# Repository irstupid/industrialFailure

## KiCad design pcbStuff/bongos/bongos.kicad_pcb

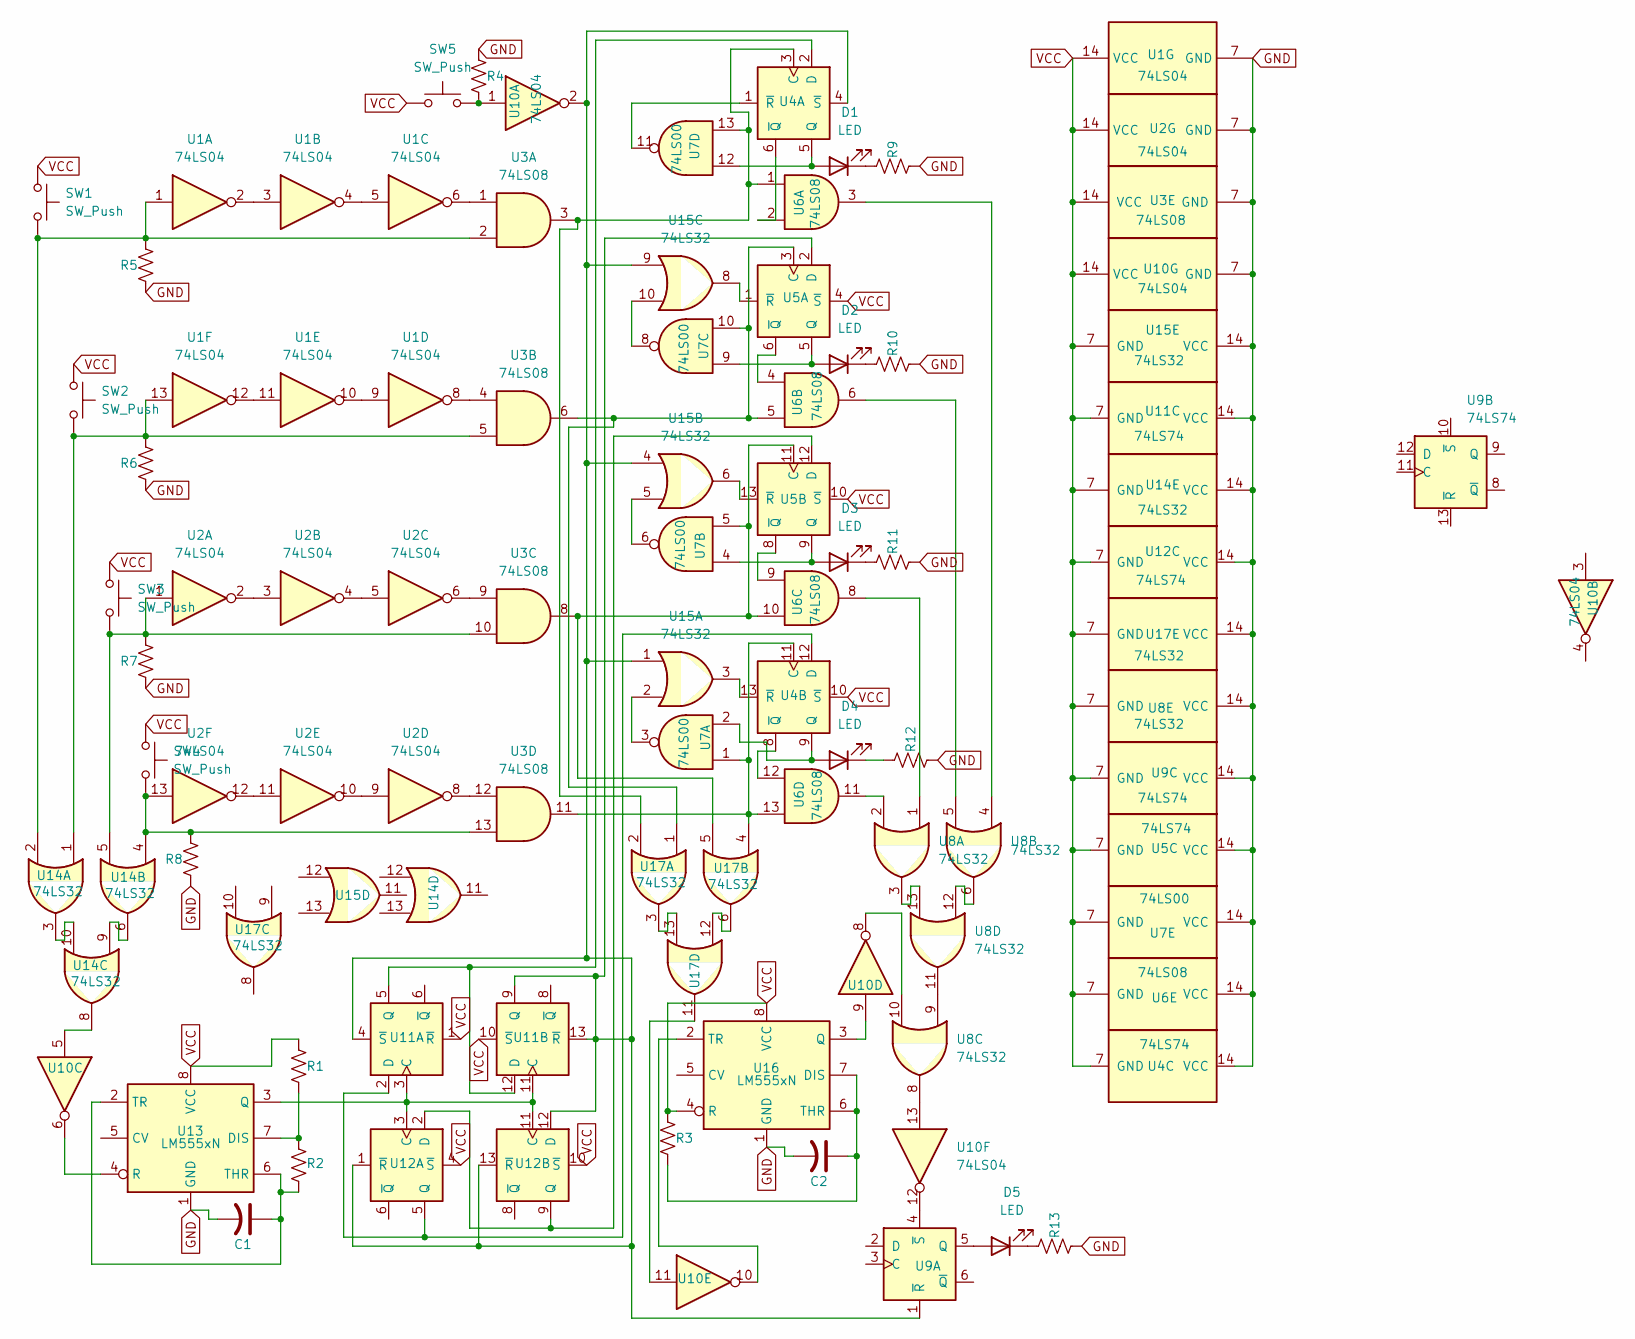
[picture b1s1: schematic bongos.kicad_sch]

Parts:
C1, C2: C_US; CP_Radial_D5.0mm_P2.50mm
D1, D2, D3, D4, D5: LED; LED_D5.0mm
R1, R2, R3, R4, R5, R6, R7, R8, R9, R10, R11, R12, R13: R_US; R_Axial_DIN0207_L6.3mm_D2.5mm_P7.62mm_Horizontal
SW1, SW2, SW3, SW4: SW_Push; SW_PUSH-12mm
SW5: SW_Push; SW_PUSH_6mm
U1, U2, U10: 74LS04; DIP-14_W7.62mm
U3, U6: 74LS08; DIP-14_W7.62mm
U4, U5, U9, U11, U12: 74LS74; DIP-14_W7.62mm
U7: 74LS00; DIP-14_W7.62mm
U8, U14, U15, U17: 74LS32; DIP-14_W7.62mm
U13, U16: LM555xN; DIP-8_W7.62mm

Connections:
GND: C1.2, C2.2, R4.1, R5.1, R6.1, R7.1, R8.1, R9.2, R10.2, R11.2, R12.2, R13.2, U1.7 (GND), U2.7 (GND), U3.7 (GND), U4.14 (VCC), U5.14 (VCC), U6.14 (VCC), U7.14 (VCC), U8.14 (VCC), U9.14 (VCC), U10.7 (GND), U11.14 (VCC), U12.14 (VCC), U13.1 (GND), U14.14 (VCC), U15.14 (VCC), U16.1 (GND), U17.14 (VCC)
unnamed: D1.2 (A), U4.5 (Q), U7.12
unnamed: D1.1 (K), R9.1
unnamed: D2.2 (A), U5.5 (Q), U7.9
unnamed: D2.1 (K), R10.1
unnamed: D3.2 (A), U5.9 (Q), U7.4
unnamed: D3.1 (K), R11.1
unnamed: D4.2 (A), U4.9 (Q), U7.2
unnamed: D4.1 (K), R12.1
unnamed: D5.2 (A), U9.5 (Q)
unnamed: D5.1 (K), R13.1
unnamed: R4.2, SW5.2, U10.1
unnamed: R5.2, SW1.2, U1.1, U3.2, U14.2
unnamed: R6.2, SW2.2, U1.13, U3.5, U14.1
unnamed: R7.2, SW3.2, U2.1, U3.10, U14.5
unnamed: R8.2, SW4.2, U2.13, U3.13, U14.4
unnamed: U1.2, U1.3
unnamed: U1.4, U1.5
unnamed: U1.6, U3.1
unnamed: U1.8, U3.4
unnamed: U1.9, U1.10
unnamed: U1.11, U1.12
unnamed: U2.2, U2.3
unnamed: U2.4, U2.5
unnamed: U2.6, U3.9
unnamed: U2.8, U3.12
unnamed: U2.9, U2.10
unnamed: U2.11, U2.12
unnamed: U3.3, U4.3 (C), U6.1, U7.13, U17.2
unnamed: U4.6 (~Q), U6.2
unnamed: U4.1 (~R), U7.11
unnamed: U3.11, U4.11 (C), U6.13, U7.1, U17.4
unnamed: U4.8 (~Q), U6.12
unnamed: U4.13 (~R), U15.3
unnamed: U3.6, U5.3 (C), U6.5, U7.10, U17.1
unnamed: U5.6 (~Q), U6.4
unnamed: U5.1 (~R), U15.8
unnamed: U3.8, U5.11 (C), U6.10, U7.5, U17.5
unnamed: U5.8 (~Q), U6.9
unnamed: U5.13 (~R), U15.6
unnamed: U6.3, U8.4
unnamed: U6.6, U8.5
unnamed: U6.8, U8.1
unnamed: U6.11, U8.2
unnamed: U8.9, U8.11
unnamed: U8.6, U8.12
unnamed: U8.3, U8.13
unnamed: U9.4 (~S), U10.12
unnamed: U10.5, U14.8
unnamed: U8.10, U10.8
unnamed: U10.11, U17.11
unnamed: U8.8, U10.13
unnamed: U11.3 (C), U11.11 (C), U12.3 (C), U12.11 (C), U13.3 (Q)
unnamed: U4.12 (D), U11.2 (D), U12.5 (Q)
unnamed: U4.2 (D), U11.5 (Q), U11.12 (D)
unnamed: U4.4 (~S), U5.2 (D), U9.1 (~R), U10.2, U11.4 (~S), U11.9 (Q), U11.13 (~R), U12.1 (~R), U12.12 (D), U12.13 (~R), U15.1, U15.4, U15.9
unnamed: U5.12 (D), U12.2 (D), U12.9 (Q)
unnamed: R1.2, R2.1, U13.7 (DIS)
unnamed: U10.6, U13.4 (R)
unnamed: C1.1, R2.2, U13.2 (TR), U13.6 (THR)
unnamed: U14.6, U14.9
unnamed: U14.3, U14.10
unnamed: U7.3, U15.2
unnamed: U7.6, U15.5
unnamed: U7.8, U15.10
unnamed: C2.1, R3.2, U16.6 (THR), U16.7 (DIS)
unnamed: U10.9, U16.3 (Q)
unnamed: U10.10, U16.2 (TR)
unnamed: U17.6, U17.12
unnamed: U17.3, U17.13
VCC: R1.1, R3.1, SW1.1, SW2.1, SW3.1, SW4.1, SW5.1, U1.14 (VCC), U2.14 (VCC), U3.14 (VCC), U4.7 (GND), U4.10 (~S), U5.4 (~S), U5.7 (GND), U5.10 (~S), U6.7 (GND), U7.7 (GND), U8.7 (GND), U9.7 (GND), U10.14 (VCC), U11.1 (~R), U11.7 (GND), U11.10 (~S), U12.4 (~S), U12.7 (GND), U12.10 (~S), U13.8 (VCC), U14.7 (GND), U15.7 (GND), U16.4 (R), U16.8 (VCC), U17.7 (GND)

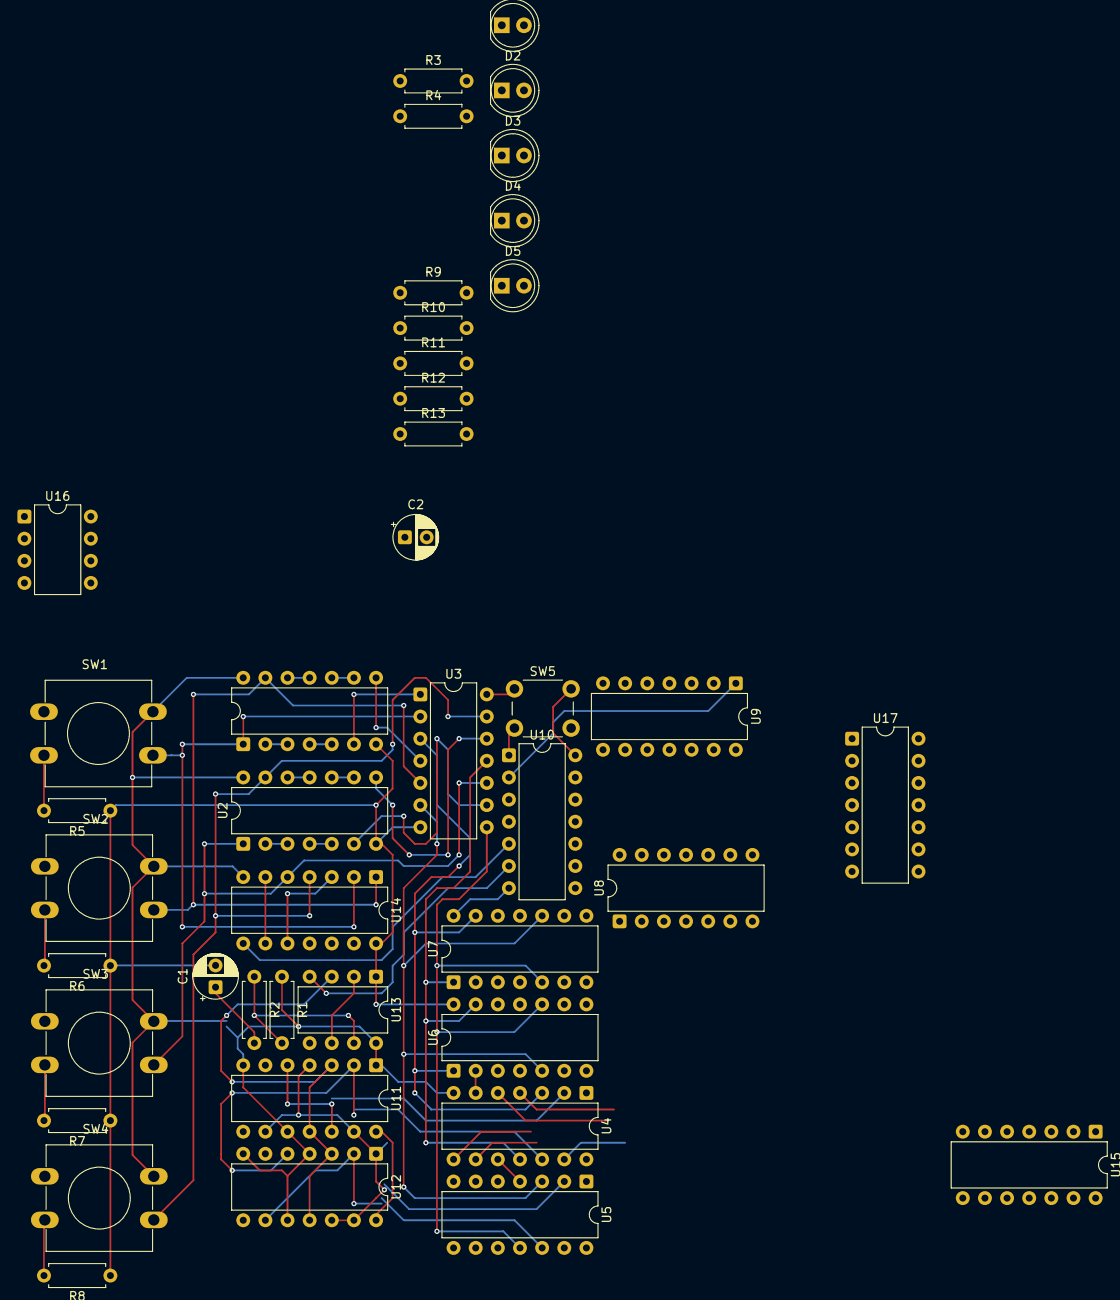
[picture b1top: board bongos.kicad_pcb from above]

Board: 2 copper layers, 42 parts (0 on the bottom side), 71 nets.

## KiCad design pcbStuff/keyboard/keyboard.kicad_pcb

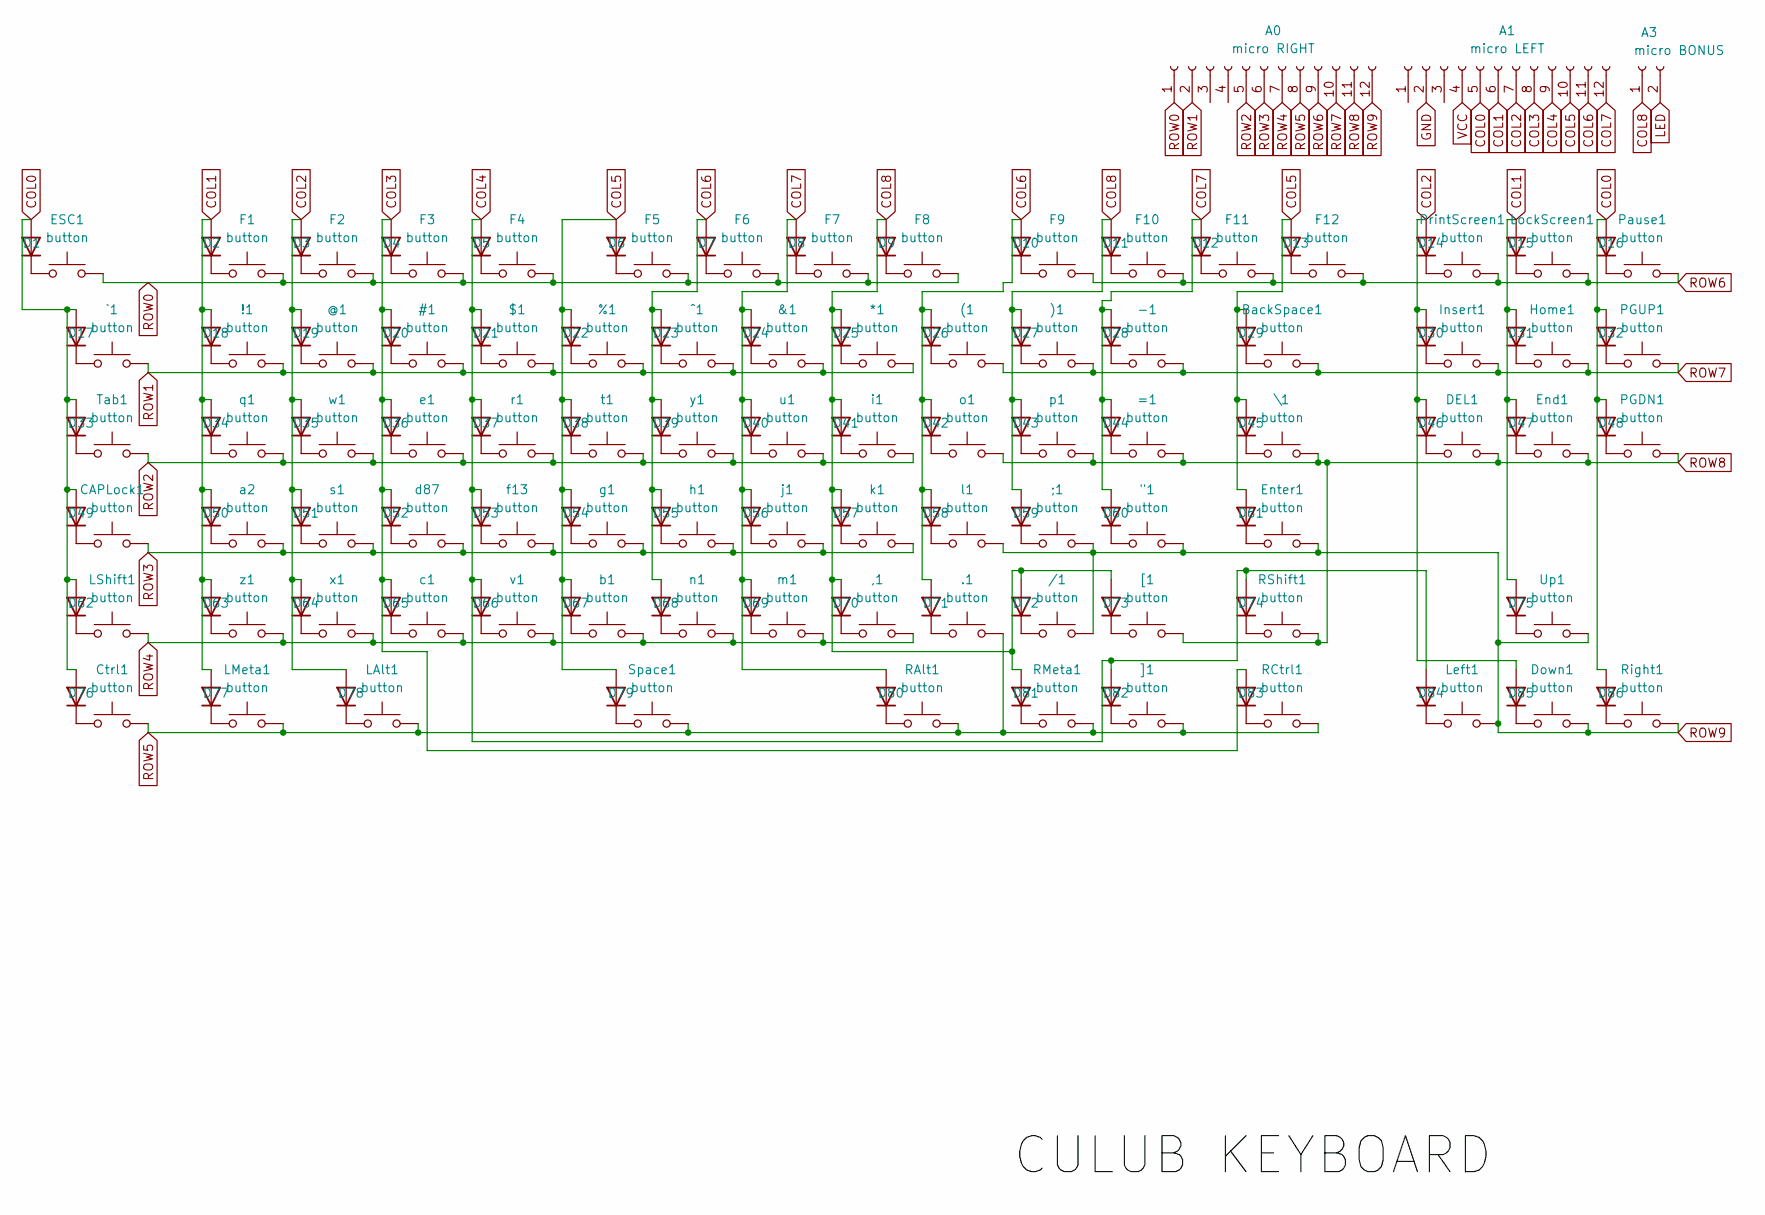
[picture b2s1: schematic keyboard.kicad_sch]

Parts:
!1: button; SW_Cherry_MX_1.00u_PCB
"1: button; SW_Cherry_MX_1.00u_PCB
$1: button; SW_Cherry_MX_1.00u_PCB
%1: button; SW_Cherry_MX_1.00u_PCB
&1: button; SW_Cherry_MX_1.00u_PCB
(1: button; SW_Cherry_MX_1.00u_PCB
)1: button; SW_Cherry_MX_1.00u_PCB
*1: button; SW_Cherry_MX_1.00u_PCB
,1: button; SW_Cherry_MX_1.00u_PCB
-1: button; SW_Cherry_MX_1.00u_PCB
.1: button; SW_Cherry_MX_1.00u_PCB
/1: button; SW_Cherry_MX_1.00u_PCB
;1: button; SW_Cherry_MX_1.00u_PCB
=1: button; SW_Cherry_MX_1.00u_PCB
@1: button; SW_Cherry_MX_1.00u_PCB
A0: micro RIGHT; PinHeader_1x12_P2.54mm_Vertical
A1: micro LEFT; PinHeader_1x12_P2.54mm_Vertical
A3: micro BONUS; PinHeader_1x02_P2.54mm_Vertical
BackSpace1: button; SW_Cherry_MX_1.00u_PCB
CAPLock1: button; SW_Cherry_MX_1.00u_PCB
Ctrl1: button; SW_Cherry_MX_1.00u_PCB
D1, D2, D3, D4, D5, D6, D7, D8, D9, D10, D11, D12, D13, D14, D15, D16, D17, D18, D19, D20, D21, D22, D23, D24, D25, D26, D27, D28, D29, D30, D31, D32, D33, D34, D35, D36, D37, D38, D39, D40, D41, D42, D43, D44, D45, D46, D47, D48, D49, D50, D51, D52, D53, D54, D55, D56, D57, D58, D59, D60, D61, D62, D63, D64, D65, D66, D67, D68, D69, D70, D71, D72, D73, D74, D75, D76, D77, D78, D79, D80, D81, D82, D83, D84, D85, D86: 1N4148WT; D_SOD-523
DEL1: button; SW_Cherry_MX_1.00u_PCB
Down1: button; SW_Cherry_MX_1.00u_PCB
ESC1: button; SW_Cherry_MX_1.00u_PCB
End1: button; SW_Cherry_MX_1.00u_PCB
Enter1: button; SW_Cherry_MX_1.00u_PCB
F1, F2, F3, F4, F5, F6, F7, F8, F9, F10, F11, F12: button; SW_Cherry_MX_1.00u_PCB
Home1: button; SW_Cherry_MX_1.00u_PCB
Insert1: button; SW_Cherry_MX_1.00u_PCB
LAlt1: button; SW_Cherry_MX_1.00u_PCB
LMeta1: button; SW_Cherry_MX_1.00u_PCB
LShift1: button; SW_Cherry_MX_1.00u_PCB
Left1: button; SW_Cherry_MX_1.00u_PCB
LockScreen1: button; SW_Cherry_MX_1.00u_PCB
PGDN1: button; SW_Cherry_MX_1.00u_PCB
PGUP1: button; SW_Cherry_MX_1.00u_PCB
Pause1: button; SW_Cherry_MX_1.00u_PCB
PrintScreen1: button; SW_Cherry_MX_1.00u_PCB
RAlt1: button; SW_Cherry_MX_1.00u_PCB
RCtrl1: button; SW_Cherry_MX_1.00u_PCB
RMeta1: button; SW_Cherry_MX_1.00u_PCB
RShift1: button; SW_Cherry_MX_1.00u_PCB
Right1: button; SW_Cherry_MX_1.00u_PCB
Space1: button; SW_Cherry_MX_1.00u_PCB
Tab1: button; SW_Cherry_MX_1.00u_PCB
Up1: button; SW_Cherry_MX_1.00u_PCB
[1: button; SW_Cherry_MX_1.00u_PCB
\1: button; SW_Cherry_MX_1.00u_PCB
]1: button; SW_Cherry_MX_1.00u_PCB
^1: button; SW_Cherry_MX_1.00u_PCB
`1: button; SW_Cherry_MX_1.00u_PCB
a2: button; SW_Cherry_MX_1.00u_PCB
b1: button; SW_Cherry_MX_1.00u_PCB
c1: button; SW_Cherry_MX_1.00u_PCB
d87: button; SW_Cherry_MX_1.00u_PCB
e1: button; SW_Cherry_MX_1.00u_PCB
f13: button; SW_Cherry_MX_1.00u_PCB
g1: button; SW_Cherry_MX_1.00u_PCB
h1: button; SW_Cherry_MX_1.00u_PCB
i1: button; SW_Cherry_MX_1.00u_PCB
j1: button; SW_Cherry_MX_1.00u_PCB
k1: button; SW_Cherry_MX_1.00u_PCB
l1: button; SW_Cherry_MX_1.00u_PCB
m1: button; SW_Cherry_MX_1.00u_PCB
n1: button; SW_Cherry_MX_1.00u_PCB
o1: button; SW_Cherry_MX_1.00u_PCB
p1: button; SW_Cherry_MX_1.00u_PCB
q1: button; SW_Cherry_MX_1.00u_PCB
r1: button; SW_Cherry_MX_1.00u_PCB
s1: button; SW_Cherry_MX_1.00u_PCB
t1: button; SW_Cherry_MX_1.00u_PCB
u1: button; SW_Cherry_MX_1.00u_PCB
v1: button; SW_Cherry_MX_1.00u_PCB
w1: button; SW_Cherry_MX_1.00u_PCB
x1: button; SW_Cherry_MX_1.00u_PCB
y1: button; SW_Cherry_MX_1.00u_PCB
z1: button; SW_Cherry_MX_1.00u_PCB

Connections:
COL0: A1.5, D1.2 (A), D16.2 (A), D17.2 (A), D32.2 (A), D33.2 (A), D48.2 (A), D49.2 (A), D62.2 (A), D76.2 (A), D86.2 (A)
COL1: A1.6, D2.2 (A), D15.2 (A), D18.2 (A), D31.2 (A), D34.2 (A), D47.2 (A), D50.2 (A), D63.2 (A), D75.2 (A), D77.2 (A)
COL2: A1.7, D3.2 (A), D14.2 (A), D19.2 (A), D30.2 (A), D35.2 (A), D46.2 (A), D51.2 (A), D64.2 (A), D78.2 (A), D85.2 (A)
COL3: A1.8, D4.2 (A), D20.2 (A), D36.2 (A), D52.2 (A), D65.2 (A), D83.2 (A)
COL4: A1.9, D5.2 (A), D21.2 (A), D37.2 (A), D53.2 (A), D66.2 (A), D74.2 (A), D82.2 (A), D84.2 (A)
COL5: A1.10, D6.2 (A), D13.2 (A), D22.2 (A), D29.2 (A), D38.2 (A), D45.2 (A), D54.2 (A), D61.2 (A), D67.2 (A), D79.2 (A)
COL6: A1.11, D7.2 (A), D10.2 (A), D23.2 (A), D26.2 (A), D39.2 (A), D42.2 (A), D55.2 (A), D58.2 (A), D68.2 (A), D71.2 (A)
COL7: A1.12, D8.2 (A), D12.2 (A), D24.2 (A), D28.2 (A), D40.2 (A), D44.2 (A), D56.2 (A), D60.2 (A), D69.2 (A), D80.2 (A)
COL8: A3.1, D9.2 (A), D11.2 (A), D25.2 (A), D27.2 (A), D41.2 (A), D43.2 (A), D57.2 (A), D59.2 (A), D70.2 (A), D72.2 (A), D73.2 (A), D81.2 (A)
GND: A1.2
LED: A3.2
unnamed: D1.1 (K), ESC1.1
unnamed: D2.1 (K), F1.1
unnamed: D3.1 (K), F2.1
unnamed: D4.1 (K), F3.1
unnamed: D5.1 (K), F4.1
unnamed: D6.1 (K), F5.1
unnamed: D7.1 (K), F6.1
unnamed: D8.1 (K), F7.1
unnamed: D9.1 (K), F8.1
unnamed: D10.1 (K), F9.1
unnamed: D11.1 (K), F10.1
unnamed: D12.1 (K), F11.1
unnamed: D13.1 (K), F12.1
unnamed: D14.1 (K), PrintScreen1.1
unnamed: D15.1 (K), LockScreen1.1
unnamed: D16.1 (K), Pause1.1
unnamed: D17.1 (K), `1.1
unnamed: !1.1, D18.1 (K)
unnamed: @1.1, D19.1 (K)
unnamed: $1.1, D21.1 (K)
unnamed: %1.1, D22.1 (K)
unnamed: D23.1 (K), ^1.1
unnamed: &1.1, D24.1 (K)
unnamed: *1.1, D25.1 (K)
unnamed: (1.1, D26.1 (K)
unnamed: )1.1, D27.1 (K)
unnamed: -1.1, D28.1 (K)
unnamed: BackSpace1.1, D29.1 (K)
unnamed: D30.1 (K), Insert1.1
unnamed: D31.1 (K), Home1.1
unnamed: D32.1 (K), PGUP1.1
unnamed: D33.1 (K), Tab1.1
unnamed: D34.1 (K), q1.1
unnamed: D35.1 (K), w1.1
unnamed: D36.1 (K), e1.1
unnamed: D37.1 (K), r1.1
unnamed: D38.1 (K), t1.1
unnamed: D39.1 (K), y1.1
unnamed: D40.1 (K), u1.1
unnamed: D41.1 (K), i1.1
unnamed: D42.1 (K), o1.1
unnamed: D43.1 (K), p1.1
unnamed: =1.1, D44.1 (K)
unnamed: D45.1 (K), \1.1
unnamed: D46.1 (K), DEL1.1
unnamed: D47.1 (K), End1.1
unnamed: D48.1 (K), PGDN1.1
unnamed: CAPLock1.1, D49.1 (K)
unnamed: D50.1 (K), a2.1
unnamed: D51.1 (K), s1.1
unnamed: D52.1 (K), d87.1
unnamed: D53.1 (K), f13.1
unnamed: D54.1 (K), g1.1
unnamed: D55.1 (K), h1.1
unnamed: D56.1 (K), j1.1
unnamed: D57.1 (K), k1.1
unnamed: D58.1 (K), l1.1
unnamed: ;1.1, D59.1 (K)
unnamed: "1.1, D60.1 (K)
unnamed: D61.1 (K), Enter1.1
unnamed: D62.1 (K), LShift1.1
unnamed: D63.1 (K), z1.1
unnamed: D64.1 (K), x1.1
unnamed: D65.1 (K), c1.1
unnamed: D66.1 (K), v1.1
unnamed: D67.1 (K), b1.1
unnamed: D68.1 (K), n1.1
unnamed: D69.1 (K), m1.1
unnamed: ,1.1, D70.1 (K)
unnamed: .1.1, D71.1 (K)
unnamed: /1.1, D72.1 (K)
unnamed: D73.1 (K), [1.1
unnamed: D74.1 (K), RShift1.1
unnamed: D75.1 (K), Up1.1
unnamed: Ctrl1.1, D76.1 (K)
unnamed: D77.1 (K), LMeta1.1
unnamed: D78.1 (K), LAlt1.1
unnamed: D79.1 (K), Space1.1
unnamed: D80.1 (K), RAlt1.1
unnamed: D81.1 (K), RMeta1.1
unnamed: D82.1 (K), ]1.1
unnamed: D83.1 (K), RCtrl1.1
unnamed: D84.1 (K), Left1.1
unnamed: D85.1 (K), Down1.1
unnamed: D86.1 (K), Right1.1
ROW0: A0.1, ESC1.2, F1.2, F2.2, F3.2, F4.2, F5.2, F6.2, F7.2, F8.2
ROW2: A0.5, Tab1.2, e1.2, i1.2, q1.2, r1.2, t1.2, u1.2, w1.2, y1.2
ROW3: A0.6, CAPLock1.2, a2.2, d87.2, f13.2, g1.2, h1.2, j1.2, k1.2, s1.2
ROW4: ,1.2, A0.7, LShift1.2, b1.2, c1.2, m1.2, n1.2, v1.2, x1.2, z1.2
ROW5: .1.2, A0.8, Ctrl1.2, LAlt1.2, LMeta1.2, RAlt1.2, RCtrl1.2, RMeta1.2, Space1.2, ]1.2
ROW6: A0.9, F9.2, F10.2, F11.2, F12.2, LockScreen1.2, Pause1.2, PrintScreen1.2
ROW7: (1.2, )1.2, -1.2, A0.10, BackSpace1.2, Home1.2, Insert1.2, PGUP1.2
ROW8: =1.2, A0.11, DEL1.2, End1.2, PGDN1.2, RShift1.2, [1.2, \1.2, o1.2, p1.2
ROW9: "1.2, /1.2, ;1.2, A0.12, Down1.2, Enter1.2, Left1.2, Right1.2, Up1.2, l1.2
VCC: A1.4

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
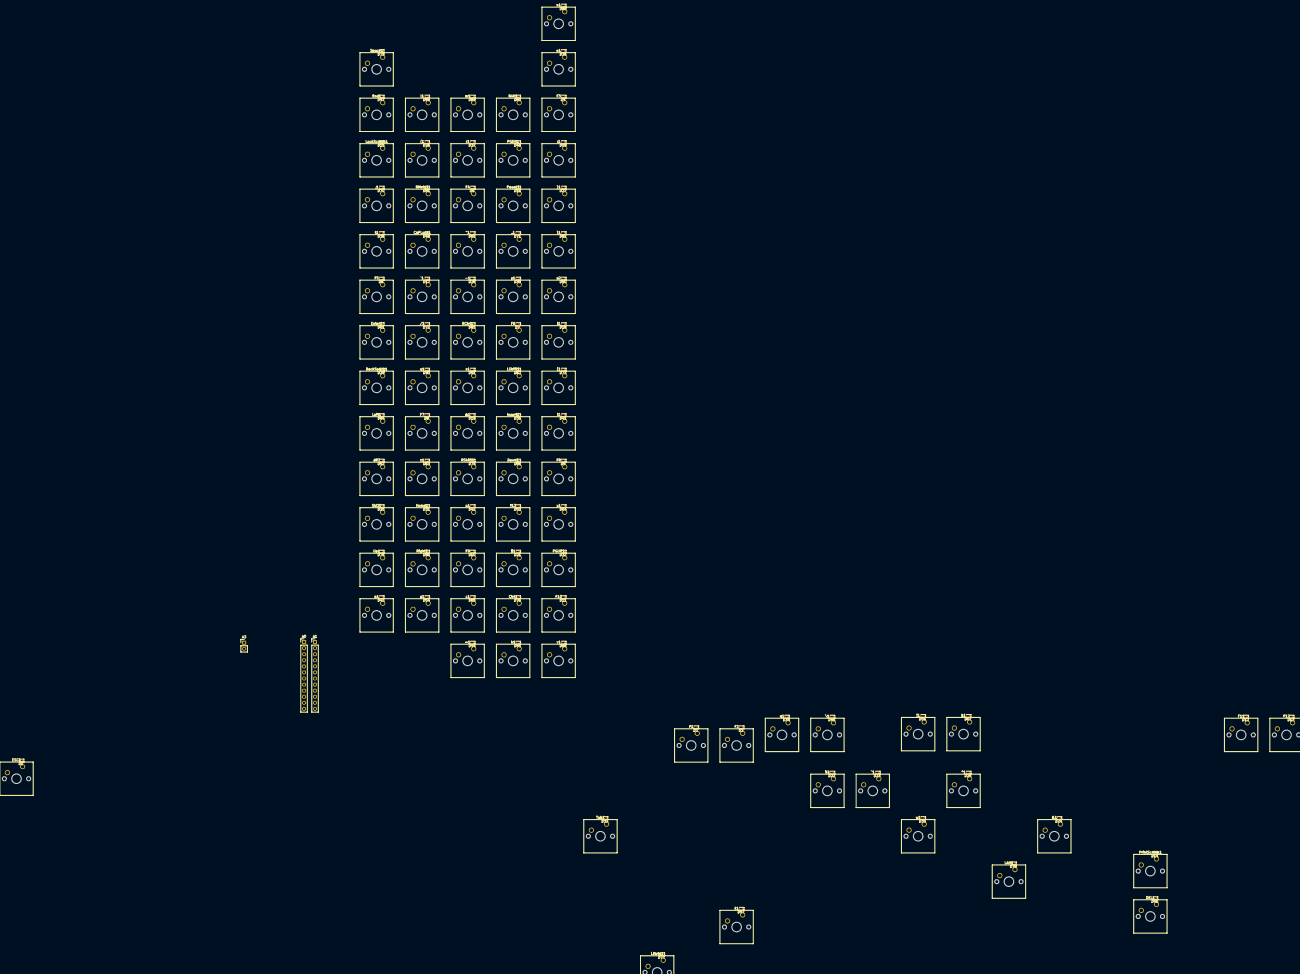
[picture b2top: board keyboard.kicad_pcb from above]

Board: 2 copper layers, 175 parts (0 on the bottom side), 105 nets.

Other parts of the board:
SW20: button; SW_Cherry_MX_1.00u_PCB

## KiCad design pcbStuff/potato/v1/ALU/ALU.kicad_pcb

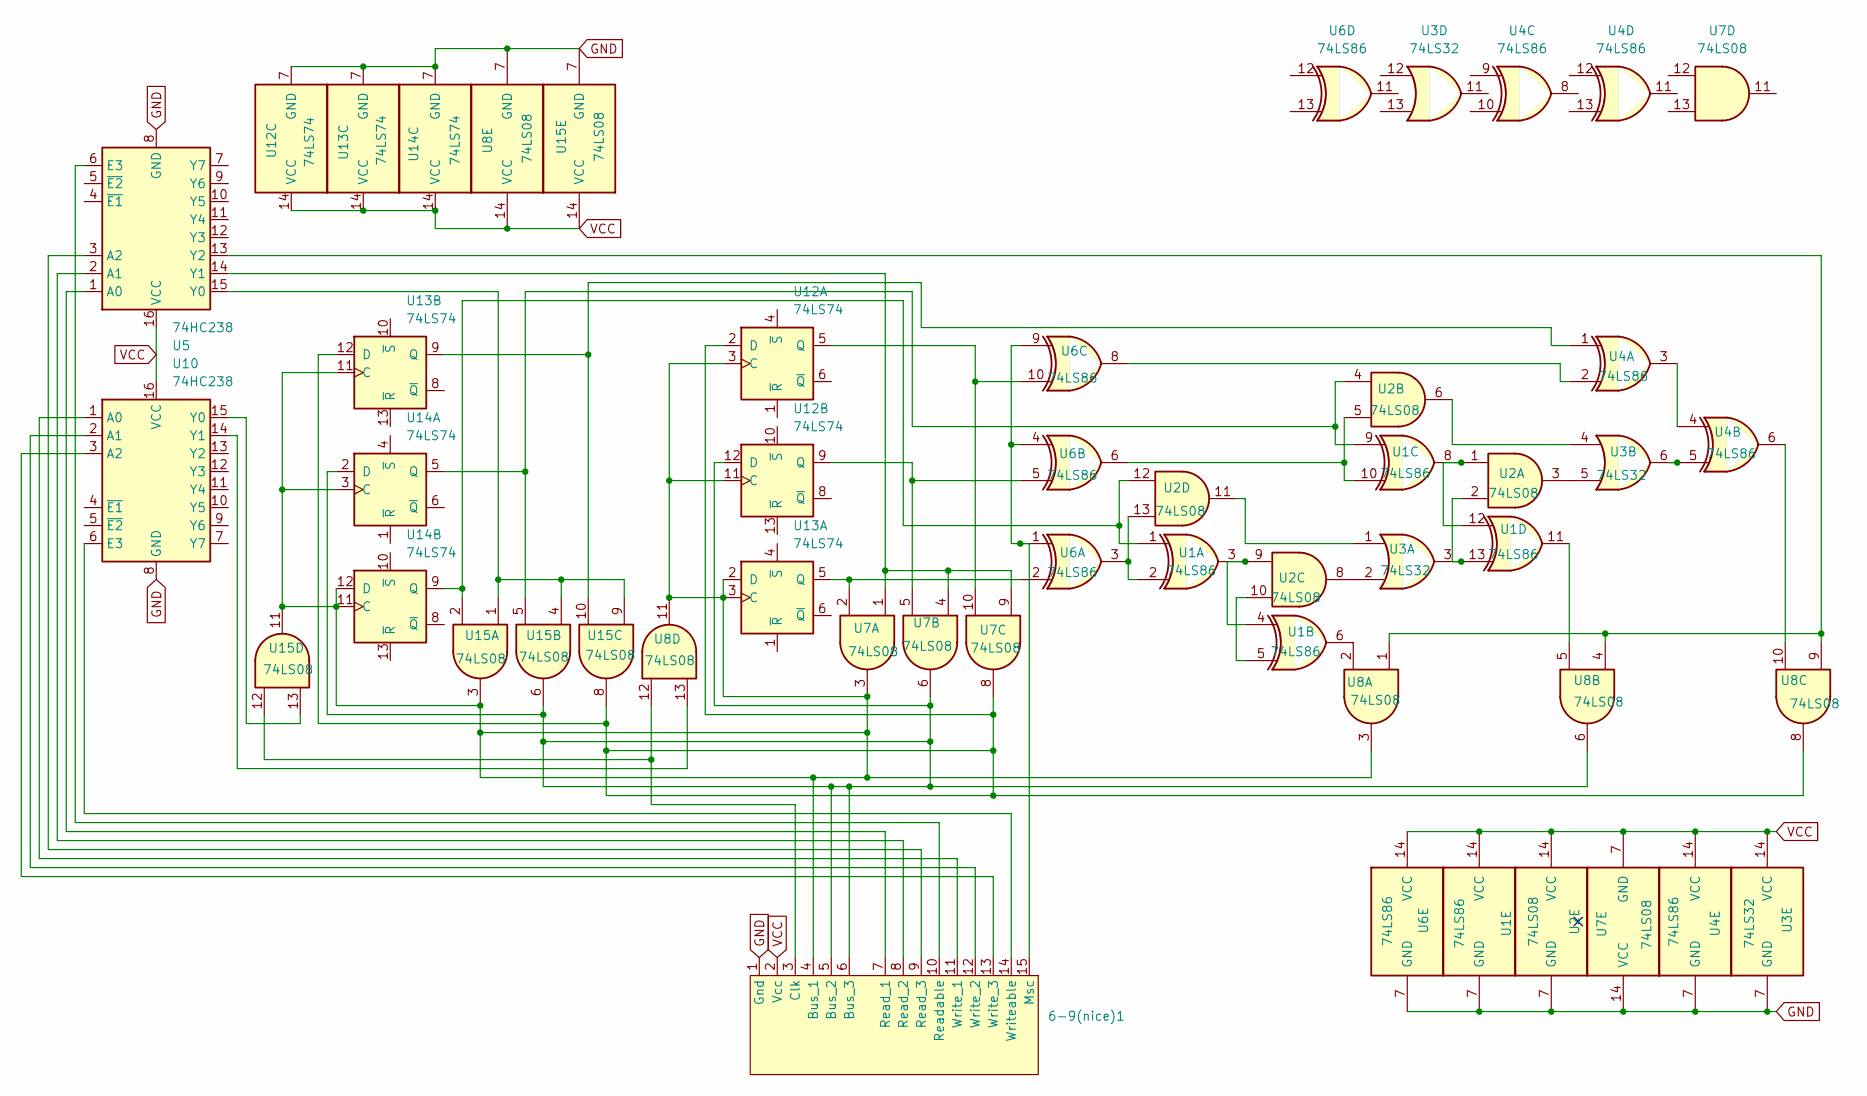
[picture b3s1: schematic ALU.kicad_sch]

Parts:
6-9(nice)1: PinHeader_1x15_P2.54mm_Vertical
U1, U4, U6: 74LS86; DIP-14_W7.62mm
U2, U7, U8, U15: 74LS08; DIP-14_W7.62mm
U3: 74LS32; DIP-14_W7.62mm
U5, U10: 74HC238; DIP-16_W7.62mm
U12, U13, U14: 74LS74; DIP-14_W7.62mm

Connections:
GND: 6-9(nice)1.1 (Gnd), U1.7 (GND), U2.7 (GND), U3.7 (GND), U4.7 (GND), U5.8 (GND), U6.7 (GND), U7.14 (VCC), U8.7 (GND), U10.8 (GND), U12.7 (GND), U13.7 (GND), U14.7 (GND), U15.7 (GND)
unnamed: 6-9(nice)1.4 (Bus_1), U7.3, U8.3, U8.11, U12.3 (C), U12.11 (C), U13.2 (D), U13.3 (C), U13.11 (C), U14.3 (C), U14.11 (C), U14.12 (D), U15.3, U15.11
unnamed: 6-9(nice)1.5 (Bus_2), 6-9(nice)1.6 (Bus_3), U7.6, U8.6, U12.12 (D), U14.2 (D), U15.6
unnamed: 6-9(nice)1.3 (Clk), U8.12, U15.12
unnamed: 6-9(nice)1.15 (Msc), U6.1, U6.4, U6.9
unnamed: 6-9(nice)1.7 (Read_1), U5.1 (A0)
unnamed: 6-9(nice)1.8 (Read_2), U5.2 (A1)
unnamed: 6-9(nice)1.9 (Read_3), U5.3 (A2)
unnamed: 6-9(nice)1.10 (Readable), U5.6 (E3)
unnamed: 6-9(nice)1.11 (Write_1), U10.1 (A0)
unnamed: 6-9(nice)1.12 (Write_2), U10.2 (A1)
unnamed: 6-9(nice)1.13 (Write_3), U10.3 (A2)
unnamed: 6-9(nice)1.14 (Writeable), U10.6 (E3)
unnamed: U1.2, U2.13, U6.3
unnamed: U1.3, U1.4, U2.9
unnamed: U1.5, U2.10
unnamed: U1.6, U8.2
unnamed: U1.10, U2.5, U6.6
unnamed: U1.11, U8.5
unnamed: U1.8, U1.12, U2.1
unnamed: U1.13, U2.2, U3.3
unnamed: U2.3, U3.5
unnamed: U2.6, U3.4
unnamed: U2.8, U3.2
unnamed: U2.11, U3.1
unnamed: U3.6, U4.5
unnamed: U4.2, U6.8
unnamed: U4.3, U4.4
unnamed: U4.6, U8.10
unnamed: U5.15 (Y0), U15.1, U15.4, U15.9
unnamed: U5.14 (Y1), U7.1, U7.4, U7.9
unnamed: U5.13 (Y2), U8.1, U8.4, U8.9
unnamed: U10.15 (Y0), U15.13
unnamed: U8.13, U10.14 (Y1)
unnamed: U7.8, U8.8, U12.2 (D), U13.12 (D), U15.8
unnamed: U6.10, U7.10, U12.5 (Q)
unnamed: U6.5, U7.5, U12.9 (Q)
unnamed: U6.2, U7.2, U13.5 (Q)
unnamed: U4.1, U13.9 (Q), U15.10
unnamed: U1.9, U2.4, U14.5 (Q), U15.5
unnamed: U1.1, U2.12, U14.9 (Q), U15.2
VCC: 6-9(nice)1.2 (Vcc), U1.14 (VCC), U2.14 (VCC), U3.14 (VCC), U4.14 (VCC), U5.16 (VCC), U6.14 (VCC), U7.7 (GND), U8.14 (VCC), U10.16 (VCC), U12.14 (VCC), U13.14 (VCC), U14.14 (VCC), U15.14 (VCC)

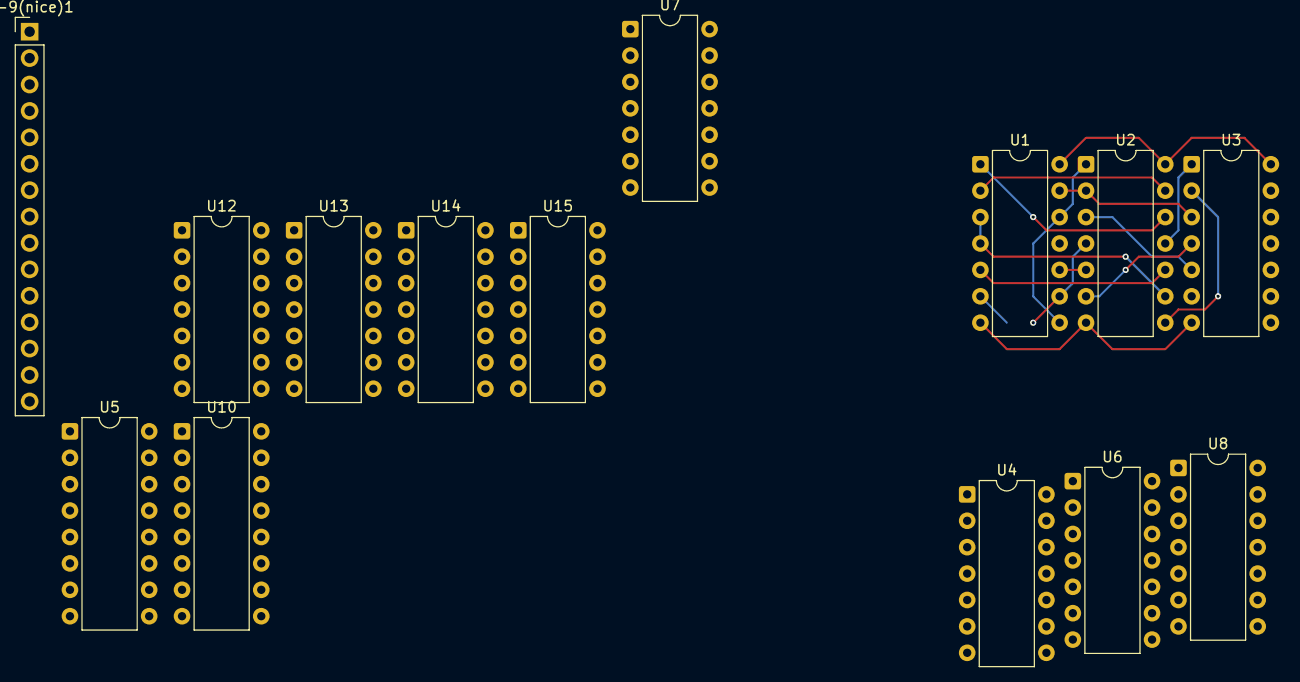
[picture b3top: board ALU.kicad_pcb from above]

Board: 2 copper layers, 14 parts (0 on the bottom side), 42 nets.

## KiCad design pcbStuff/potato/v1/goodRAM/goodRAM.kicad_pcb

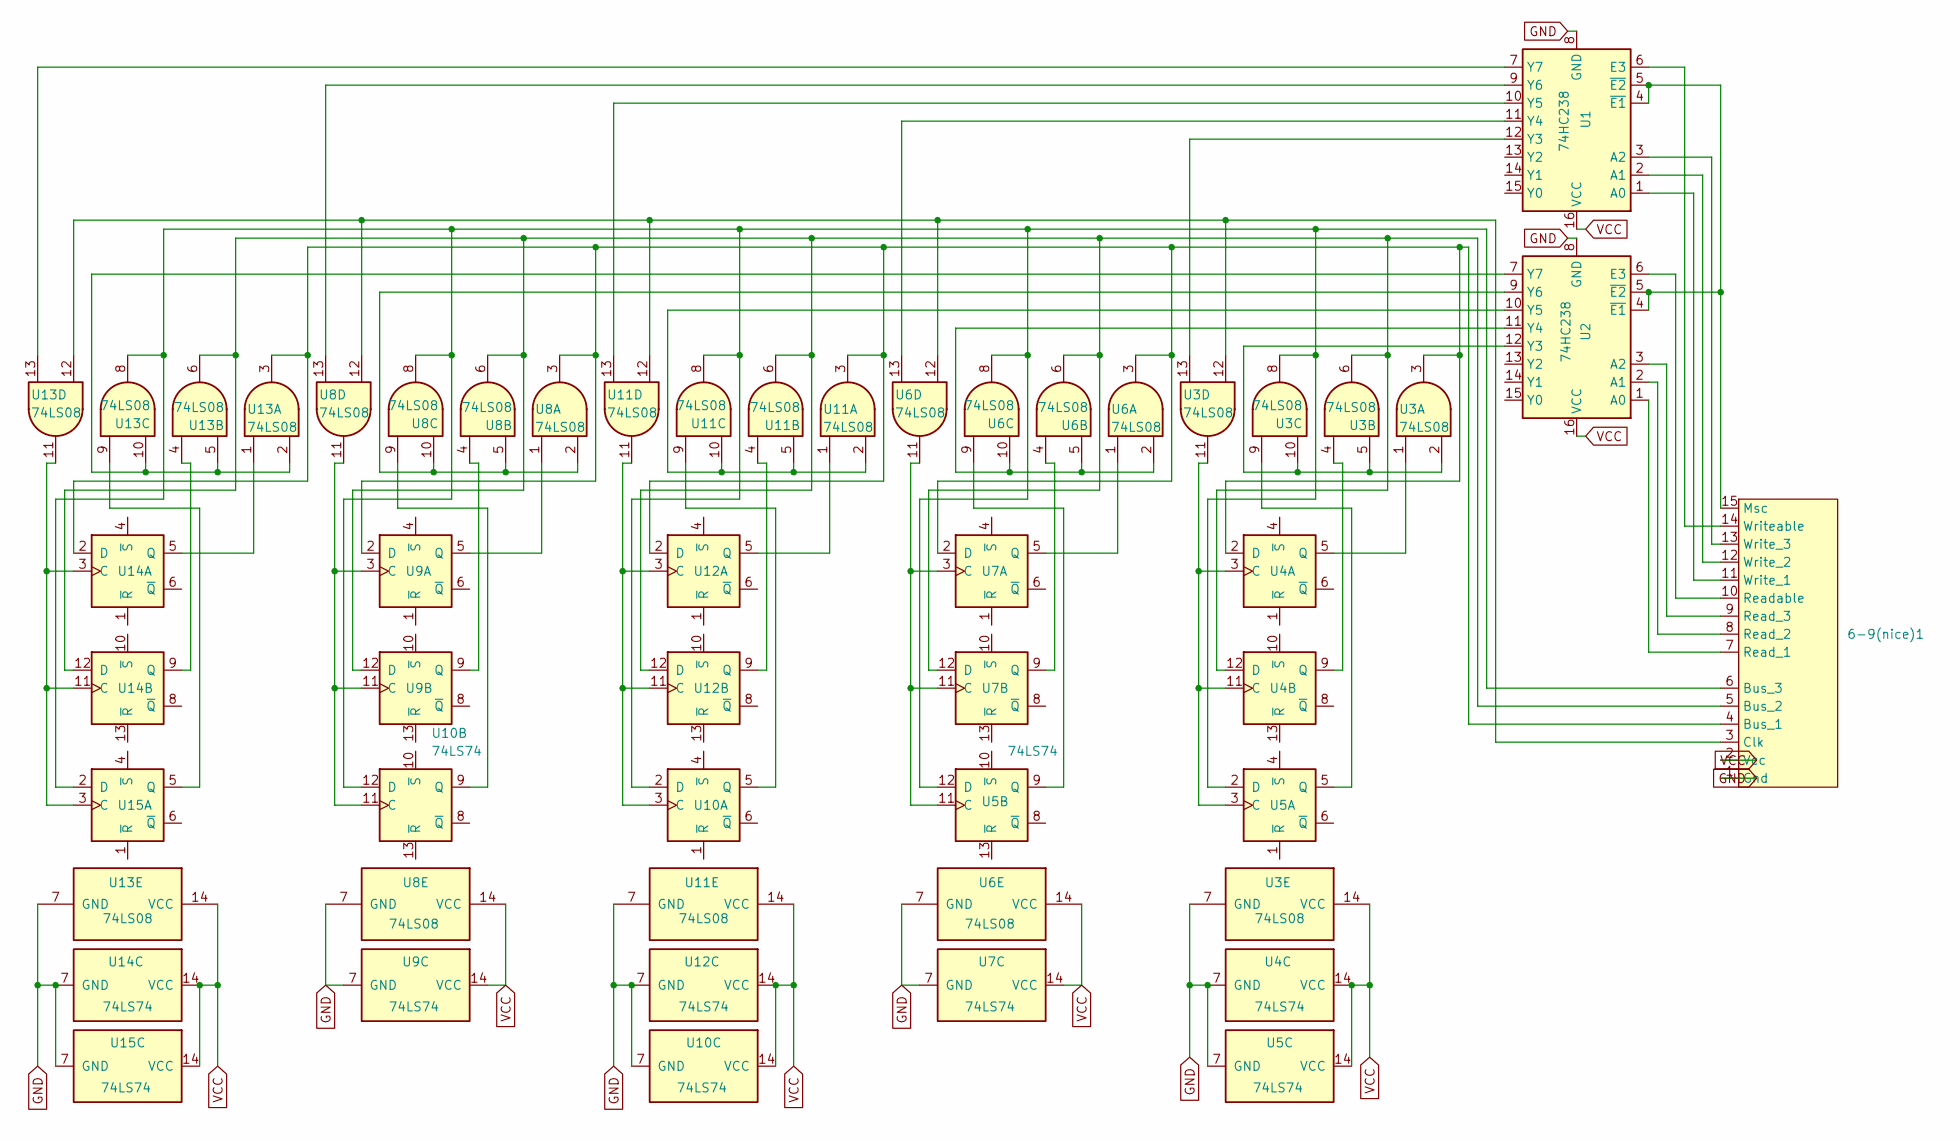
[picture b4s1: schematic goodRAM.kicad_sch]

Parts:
6-9(nice)1: PinHeader_1x15_P2.54mm_Vertical
U1, U2: 74HC238; DIP-16_W7.62mm
U3, U6, U8, U11, U13: 74LS08; DIP-14_W7.62mm
U4, U5, U7, U9, U10, U12, U14, U15: 74LS74; DIP-14_W7.62mm

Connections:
GND: 6-9(nice)1.1 (Gnd), U1.8 (GND), U2.8 (GND), U3.7 (GND), U4.7 (GND), U5.7 (GND), U6.7 (GND), U7.7 (GND), U8.7 (GND), U9.7 (GND), U10.7 (GND), U11.7 (GND), U12.7 (GND), U13.7 (GND), U14.7 (GND), U15.7 (GND)
unnamed: 6-9(nice)1.4 (Bus_1), U3.3, U4.2 (D), U6.3, U7.2 (D), U8.3, U9.2 (D), U11.3, U12.2 (D), U13.3, U14.2 (D)
unnamed: 6-9(nice)1.5 (Bus_2), U3.6, U4.12 (D), U6.6, U7.12 (D), U8.6, U9.12 (D), U11.6, U12.12 (D), U13.6, U14.12 (D)
unnamed: 6-9(nice)1.6 (Bus_3), U3.8, U5.2 (D), U5.12 (D), U6.8, U8.8, U10.2 (D), U10.12 (D), U11.8, U13.8, U15.2 (D)
unnamed: 6-9(nice)1.3 (Clk), U3.12, U6.12, U8.12, U11.12, U13.12
unnamed: 6-9(nice)1.15 (Msc), U1.4 (~E1), U1.5 (~E2), U2.4 (~E1), U2.5 (~E2)
unnamed: 6-9(nice)1.7 (Read_1), U2.1 (A0)
unnamed: 6-9(nice)1.8 (Read_2), U2.2 (A1)
unnamed: 6-9(nice)1.9 (Read_3), U2.3 (A2)
unnamed: 6-9(nice)1.10 (Readable), U2.6 (E3)
unnamed: 6-9(nice)1.11 (Write_1), U1.1 (A0)
unnamed: 6-9(nice)1.12 (Write_2), U1.2 (A1)
unnamed: 6-9(nice)1.13 (Write_3), U1.3 (A2)
unnamed: 6-9(nice)1.14 (Writeable), U1.6 (E3)
unnamed: U1.12 (Y3), U3.13
unnamed: U1.11 (Y4), U6.13
unnamed: U1.10 (Y5), U11.13
unnamed: U1.9 (Y6), U8.13
unnamed: U1.7 (Y7), U13.13
unnamed: U2.12 (Y3), U3.2, U3.5, U3.10
unnamed: U2.11 (Y4), U6.2, U6.5, U6.10
unnamed: U2.10 (Y5), U11.2, U11.5, U11.10
unnamed: U2.9 (Y6), U8.2, U8.5, U8.10
unnamed: U2.7 (Y7), U13.2, U13.5, U13.10
unnamed: U3.11, U4.3 (C), U4.11 (C), U5.3 (C)
unnamed: U3.1, U4.5 (Q)
unnamed: U3.4, U4.9 (Q)
unnamed: U3.9, U5.5 (Q)
unnamed: U5.11 (C), U6.11, U7.3 (C), U7.11 (C)
unnamed: U5.9 (Q), U6.9
unnamed: U6.1, U7.5 (Q)
unnamed: U6.4, U7.9 (Q)
unnamed: U8.1, U9.5 (Q)
unnamed: U8.4, U9.9 (Q)
unnamed: U10.3 (C), U11.11, U12.3 (C), U12.11 (C)
unnamed: U10.5 (Q), U11.9
unnamed: U8.11, U9.3 (C), U9.11 (C), U10.11 (C)
unnamed: U8.9, U10.9 (Q)
unnamed: U11.1, U12.5 (Q)
unnamed: U11.4, U12.9 (Q)
unnamed: U13.11, U14.3 (C), U14.11 (C), U15.3 (C)
unnamed: U13.1, U14.5 (Q)
unnamed: U13.4, U14.9 (Q)
unnamed: U13.9, U15.5 (Q)
VCC: 6-9(nice)1.2 (Vcc), U1.16 (VCC), U2.16 (VCC), U3.14 (VCC), U4.14 (VCC), U5.14 (VCC), U6.14 (VCC), U7.14 (VCC), U8.14 (VCC), U9.14 (VCC), U10.14 (VCC), U11.14 (VCC), U12.14 (VCC), U13.14 (VCC), U14.14 (VCC), U15.14 (VCC)
